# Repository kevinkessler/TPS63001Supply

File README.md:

KiCad files for a Buck/Boost Converter using the TPS63001 or TPS63002
This version is for JLCPCB SMT Assembly minimum size of 20mmx20mm

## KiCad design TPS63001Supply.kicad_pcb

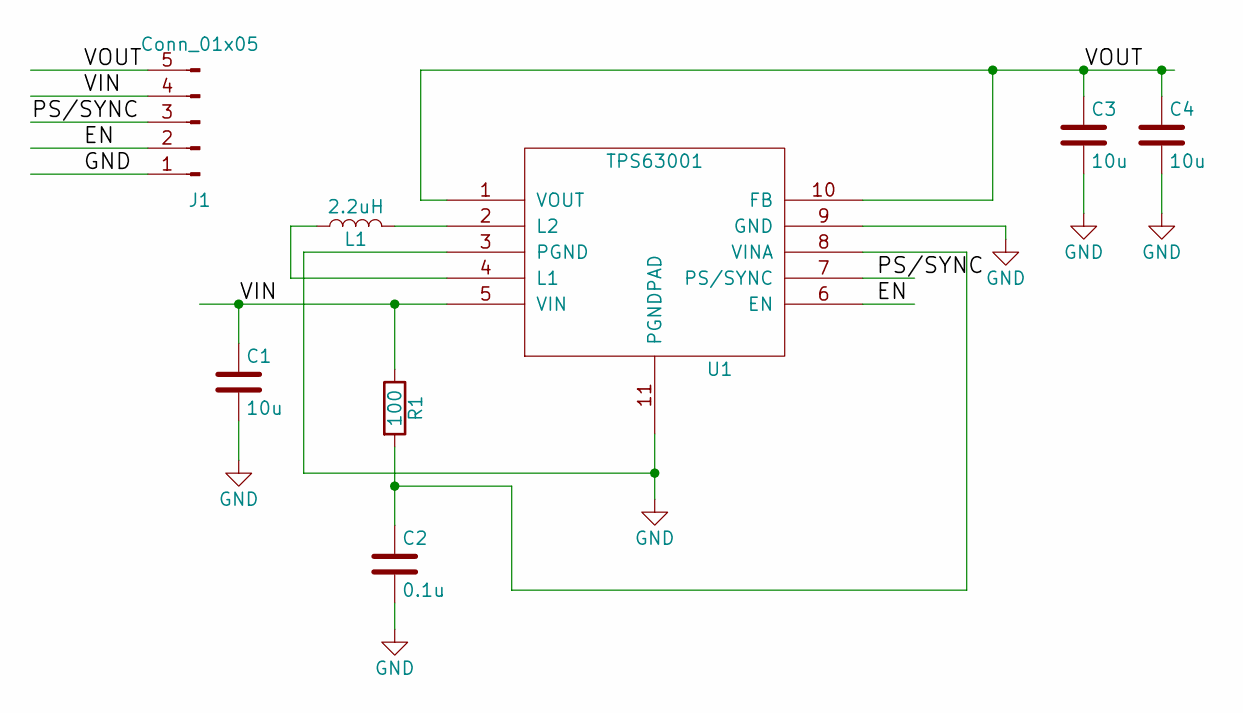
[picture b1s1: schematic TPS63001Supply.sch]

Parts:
C1, C3, C4: 10u; C_0805_2012Metric_Pad1.15x1.40mm_HandSolder; LCSC C15850
C2: 0.1u; C_0805_2012Metric_Pad1.15x1.40mm_HandSolder; LCSC C49678
J1: Conn_01x05; PinHeader_1x05_P2.54mm_Vertical
L1: 2.2uH; L_1210_3225Metric_Pad1.42x2.65mm_HandSolder; LCSC C341775
R1: 100; R_0805_2012Metric_Pad1.15x1.40mm_HandSolder; LCSC C17408
U1: TPS63001; TPS63000; LCSC C28060

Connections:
/EN: J1.2, U1.6 (EN)
/PS/SYNC: J1.3, U1.7 (PS/SYNC)
/VIN: C1.1, J1.4, R1.1, U1.5 (VIN)
/VOUT: C3.1, C4.1, J1.5, U1.1 (VOUT), U1.10 (FB)
GND: C1.2, C2.2, C3.2, C4.2, J1.1, U1.3 (PGND), U1.9 (GND), U1.11 (PGNDPAD)
unnamed: C2.1, R1.2, U1.8 (VINA)
unnamed: L1.1, U1.4 (L1)
unnamed: L1.2, U1.2 (L2)

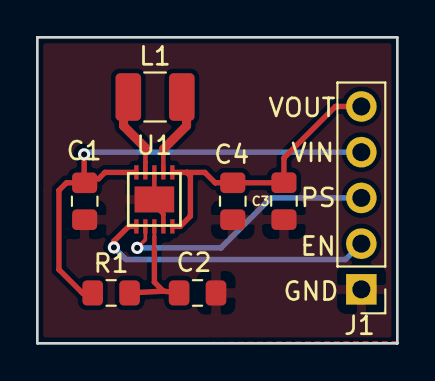
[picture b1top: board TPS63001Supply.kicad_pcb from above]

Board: 2 copper layers, 20.0 x 17.0 mm, 8 parts (0 on the bottom side), 8 nets.

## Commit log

2020-09-01 OSH Park version
2020-09-02 JCLPCB
2020-10-07 Add Labels
